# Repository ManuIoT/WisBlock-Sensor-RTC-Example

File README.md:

# WisBlock-Sensor-RTC-Example
This is a KiCAD version of the WisBlock-Sensor-RTC-Example original from Eagle files [RAKwireless WisBlock](https://docs.rakwireless.com/Product-Categories/WisBlock/

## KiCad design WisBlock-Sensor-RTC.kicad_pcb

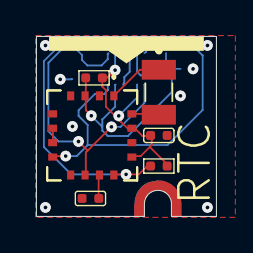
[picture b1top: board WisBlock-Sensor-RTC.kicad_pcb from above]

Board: 2 copper layers, 10.0 x 10.0 mm, 9 parts (0 on the bottom side), 10 nets.

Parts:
C1: 100nf; C0402
C2: 47PF; C0402
IC1: CBC34803-M5C; CBC34803M5C
J1: FBB04004-M24S1003K6M; FBB04004M24S1003K6M
R1, R2: 10K 1/16W; R0402
U$1: RAK_SENSOR_FIX
U$12: RAK_LOGO; WISBLOCK_LOGO
Y1: ABS07-166-32.768KHZ-T; ABS0716632768KHZT

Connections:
+3V3: C1.2, IC1.13, IC1.15, J1.9, J1.16, R1.2, R2.2
/AF: C2.2, IC1.11
/FOUT: IC1.12, J1.12, J1.13, R2.1
/I2C1_SCL: IC1.10, J1.7, J1.18
/I2C1_SDA: IC1.8, J1.8, J1.17
/IRQ2: IC1.3, J1.10, J1.15, R1.1
GND: C1.1, C2.1, IC1.5, J1.2, J1.23, J1.MP1, J1.MP2, J1.MP3, J1.MP4, U$1.P$1, U$1.P$2
unnamed: IC1.1, Y1.1
unnamed: IC1.6, IC1.7
unnamed: IC1.16, Y1.2

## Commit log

2020-11-27 Add files via upload
    RAKwireless WisBlock RTC-Sensor-Example from Eagle to KiCAD
2020-11-27 Create a Readme.md
    This is a KiCAD version from the Eagle RAK Wisblock example
2020-11-27 Add files via upload
    All files are unziped , library manager call for 3D parts must be checked in order to point to the main folder
